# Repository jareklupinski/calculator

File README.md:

# calculator
An open TI-84-inspired mathematical device

This design will be fun to play with for a while.

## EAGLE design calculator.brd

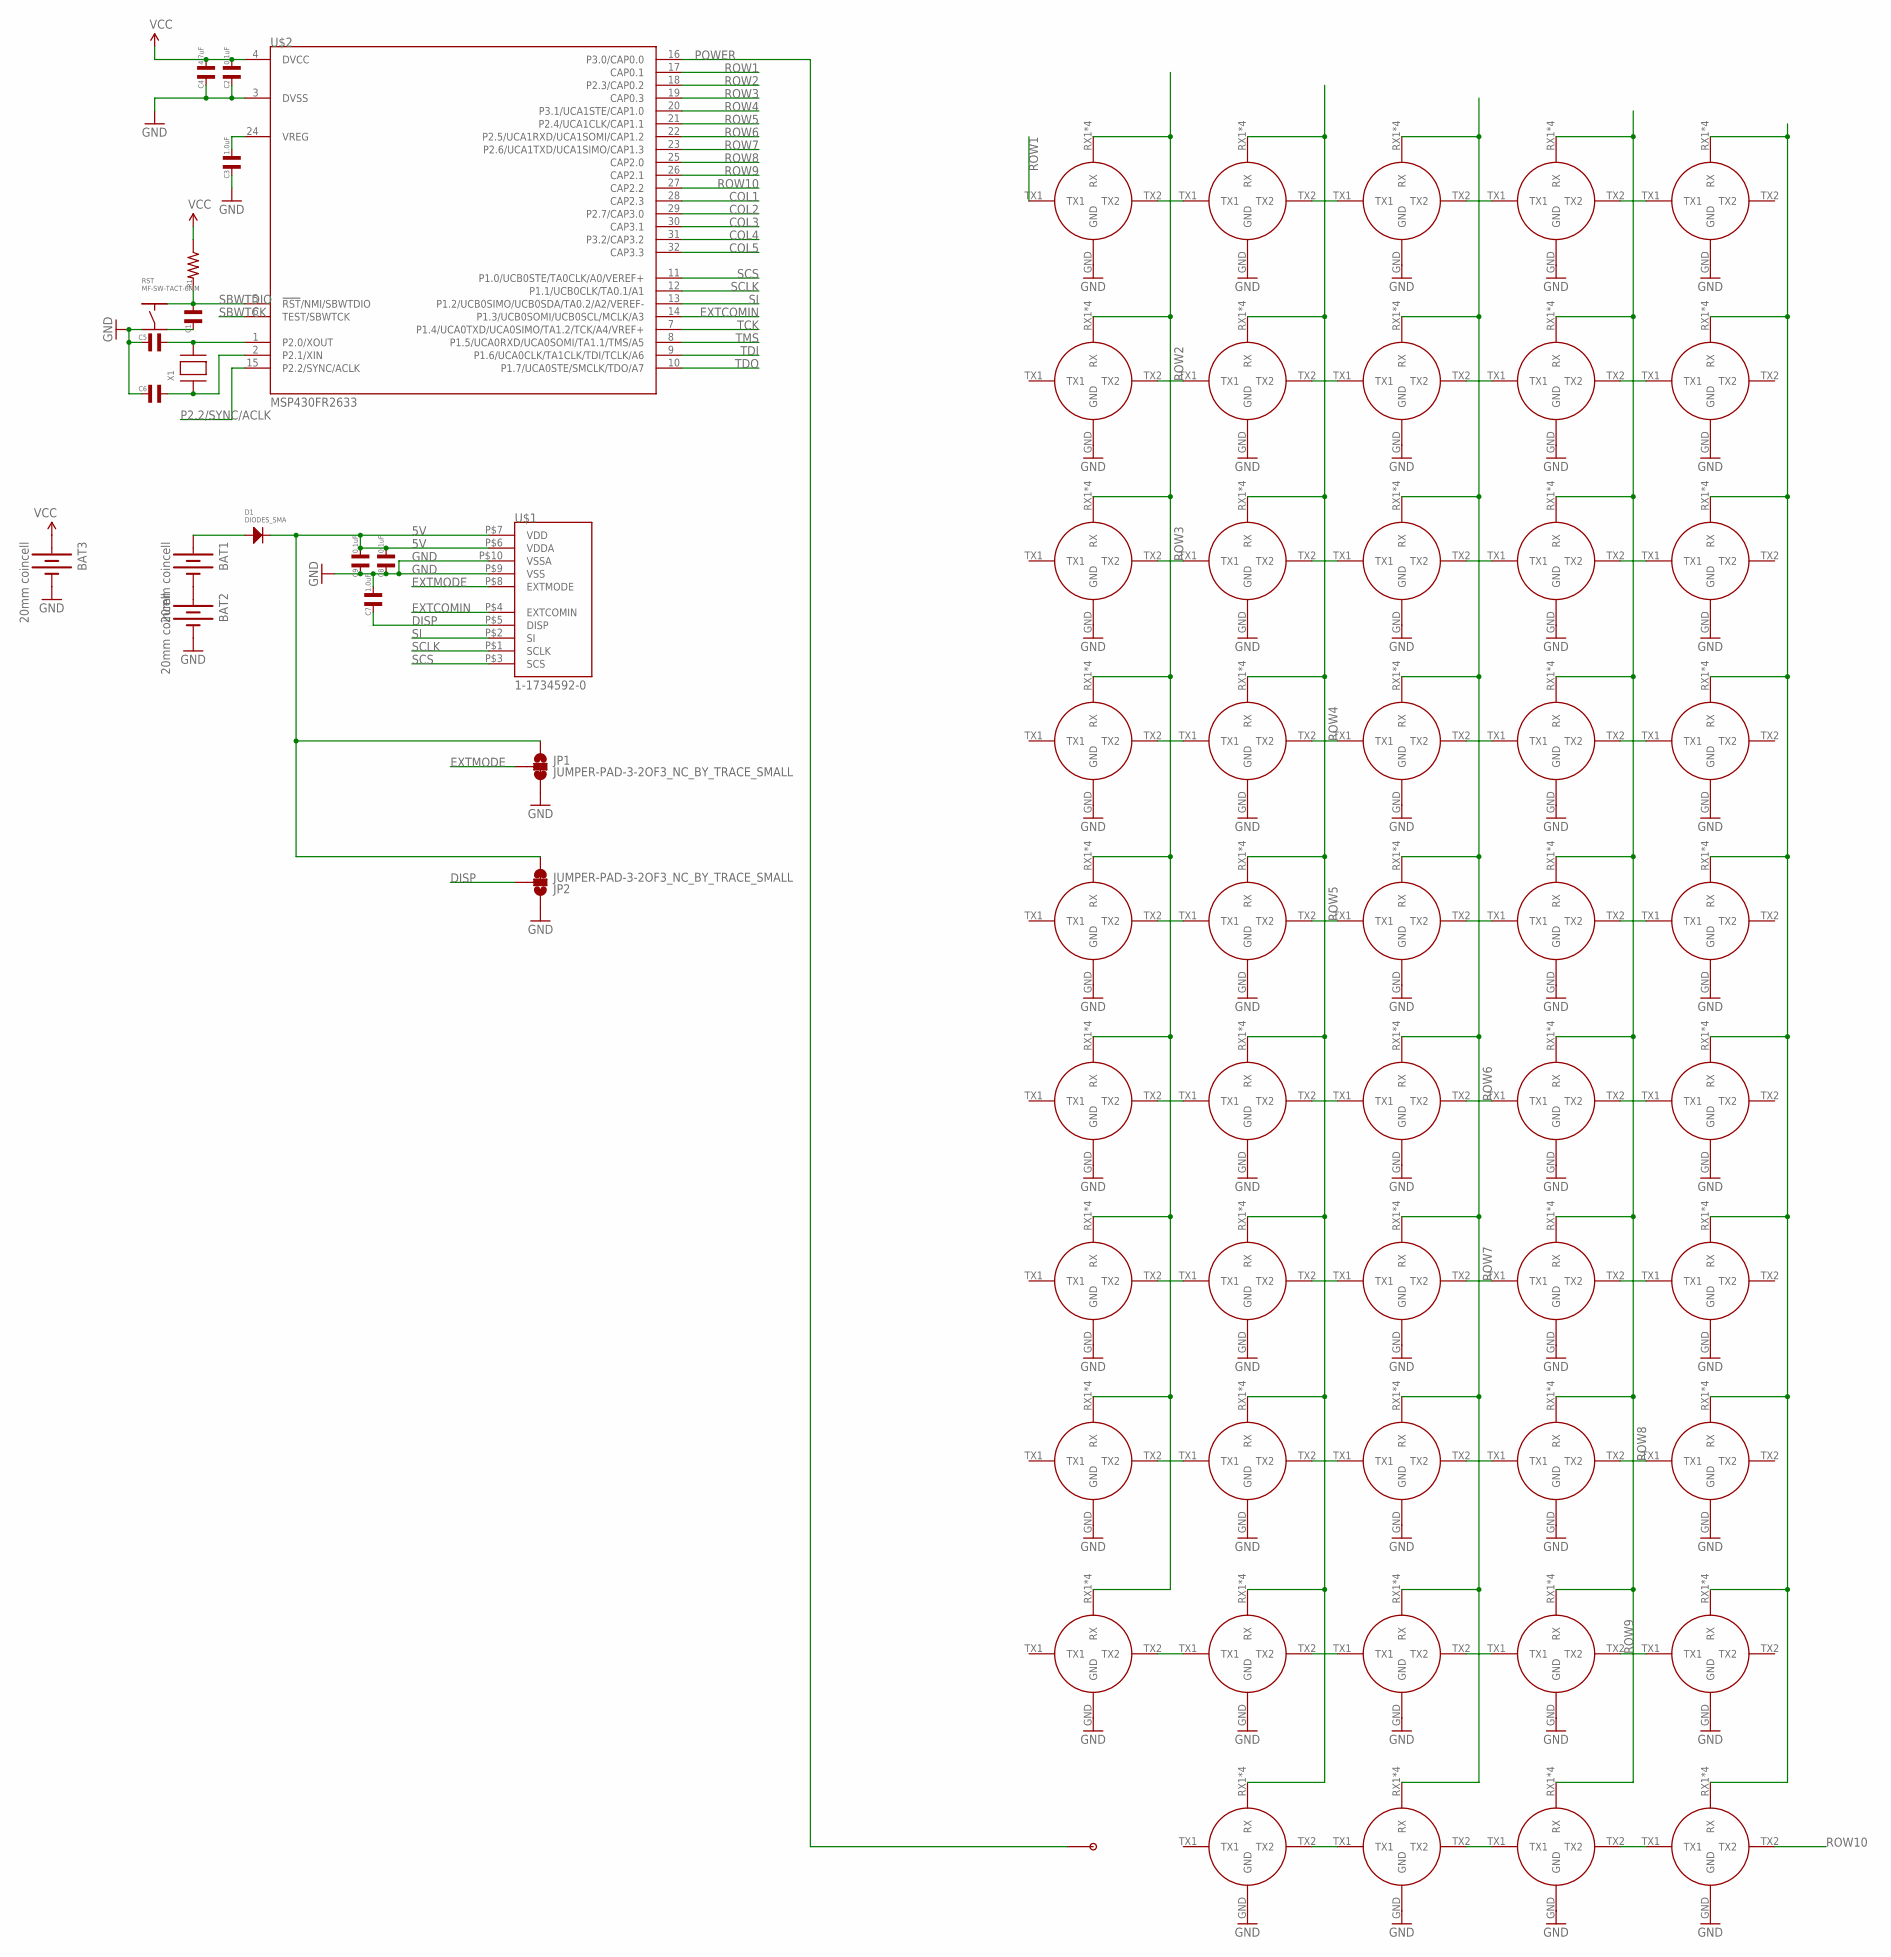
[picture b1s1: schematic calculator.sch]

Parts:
BAT1, BAT2, BAT3: 20mm coincell; BATTCON_20MM_4LEGS
C1: CAPACITOR_NP_0603; C0603
C2, C8, C9: 0.1uF; C0603
C3, C7: 1.0uF; C0603
C4: 4.7uF; C0603
C5, C6: CAPACITOR_NP_0402; C0402
D1: DIODES_SMA; SMA
JP1, JP2: JUMPER-PAD-3-2OF3_NC_BY_TRACE_SMALL; PAD-JUMPER-3-2OF3_NC_BY_TRACE_YES_SILK_FULL_BOX
P1: CAPPADPAD; CAPTOUCHBTN2
R1: RESISTOR_0603; R0603
RST: MF-SW-TACT-6MM; TACT6MM
U$1: 1-1734592-0
U$2: MSP430FR2633; TSSOP32
U$3, U$4, U$5, U$6, U$7, U$8, U$9, U$10, U$11, U$12, U$13, U$14, U$15, U$16, U$17, U$18, U$19, U$20, U$21, U$22, U$23, U$24, U$25, U$26, U$27, U$28, U$29, U$30, U$31, U$32, U$33, U$34, U$35, U$36, U$37, U$38, U$39, U$40, U$41, U$42, U$43, U$44, U$45, U$46, U$47, U$48, U$49, U$50, U$51: CAPTOUCH; CAPTOUCHBTN
X1: XTAL-3.2X1.5; XTAL3215

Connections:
5V: C8.P$1, C9.P$1, D1.CATHODE, JP1.1, JP2.3, U$1.P$6 (VDDA), U$1.P$7 (VDD)
COL1: U$2.28 (CAP2.3), U$3.RX1 (RX), U$3.RX2 (RX), U$3.RX3 (RX), U$3.RX4 (RX), U$8.RX1 (RX), U$8.RX2 (RX), U$8.RX3 (RX), U$8.RX4 (RX), U$13.RX1 (RX), U$13.RX2 (RX), U$13.RX3 (RX), U$13.RX4 (RX), U$18.RX1 (RX), U$18.RX2 (RX), U$18.RX3 (RX), U$18.RX4 (RX), U$23.RX1 (RX), U$23.RX2 (RX), U$23.RX3 (RX), U$23.RX4 (RX), U$28.RX1 (RX), U$28.RX2 (RX), U$28.RX3 (RX), U$28.RX4 (RX), U$33.RX1 (RX), U$33.RX2 (RX), U$33.RX3 (RX), U$33.RX4 (RX), U$38.RX1 (RX), U$38.RX2 (RX), U$38.RX3 (RX), U$38.RX4 (RX), U$43.RX1 (RX), U$43.RX2 (RX), U$43.RX3 (RX), U$43.RX4 (RX)
COL2: U$2.29 (P2.7/CAP3.0), U$4.RX1 (RX), U$4.RX2 (RX), U$4.RX3 (RX), U$4.RX4 (RX), U$9.RX1 (RX), U$9.RX2 (RX), U$9.RX3 (RX), U$9.RX4 (RX), U$14.RX1 (RX), U$14.RX2 (RX), U$14.RX3 (RX), U$14.RX4 (RX), U$19.RX1 (RX), U$19.RX2 (RX), U$19.RX3 (RX), U$19.RX4 (RX), U$24.RX1 (RX), U$24.RX2 (RX), U$24.RX3 (RX), U$24.RX4 (RX), U$29.RX1 (RX), U$29.RX2 (RX), U$29.RX3 (RX), U$29.RX4 (RX), U$34.RX1 (RX), U$34.RX2 (RX), U$34.RX3 (RX), U$34.RX4 (RX), U$39.RX1 (RX), U$39.RX2 (RX), U$39.RX3 (RX), U$39.RX4 (RX), U$44.RX1 (RX), U$44.RX2 (RX), U$44.RX3 (RX), U$44.RX4 (RX), U$48.RX1 (RX), U$48.RX2 (RX), U$48.RX3 (RX), U$48.RX4 (RX)
COL3: U$2.30 (CAP3.1), U$5.RX1 (RX), U$5.RX2 (RX), U$5.RX3 (RX), U$5.RX4 (RX), U$10.RX1 (RX), U$10.RX2 (RX), U$10.RX3 (RX), U$10.RX4 (RX), U$15.RX1 (RX), U$15.RX2 (RX), U$15.RX3 (RX), U$15.RX4 (RX), U$20.RX1 (RX), U$20.RX2 (RX), U$20.RX3 (RX), U$20.RX4 (RX), U$25.RX1 (RX), U$25.RX2 (RX), U$25.RX3 (RX), U$25.RX4 (RX), U$30.RX1 (RX), U$30.RX2 (RX), U$30.RX3 (RX), U$30.RX4 (RX), U$35.RX1 (RX), U$35.RX2 (RX), U$35.RX3 (RX), U$35.RX4 (RX), U$40.RX1 (RX), U$40.RX2 (RX), U$40.RX3 (RX), U$40.RX4 (RX), U$45.RX1 (RX), U$45.RX2 (RX), U$45.RX3 (RX), U$45.RX4 (RX), U$49.RX1 (RX), U$49.RX2 (RX), U$49.RX3 (RX), U$49.RX4 (RX)
COL4: U$2.31 (P3.2/CAP3.2), U$6.RX1 (RX), U$6.RX2 (RX), U$6.RX3 (RX), U$6.RX4 (RX), U$11.RX1 (RX), U$11.RX2 (RX), U$11.RX3 (RX), U$11.RX4 (RX), U$16.RX1 (RX), U$16.RX2 (RX), U$16.RX3 (RX), U$16.RX4 (RX), U$21.RX1 (RX), U$21.RX2 (RX), U$21.RX3 (RX), U$21.RX4 (RX), U$26.RX1 (RX), U$26.RX2 (RX), U$26.RX3 (RX), U$26.RX4 (RX), U$31.RX1 (RX), U$31.RX2 (RX), U$31.RX3 (RX), U$31.RX4 (RX), U$36.RX1 (RX), U$36.RX2 (RX), U$36.RX3 (RX), U$36.RX4 (RX), U$41.RX1 (RX), U$41.RX2 (RX), U$41.RX3 (RX), U$41.RX4 (RX), U$46.RX1 (RX), U$46.RX2 (RX), U$46.RX3 (RX), U$46.RX4 (RX), U$50.RX1 (RX), U$50.RX2 (RX), U$50.RX3 (RX), U$50.RX4 (RX)
COL5: U$2.32 (CAP3.3), U$7.RX1 (RX), U$7.RX2 (RX), U$7.RX3 (RX), U$7.RX4 (RX), U$12.RX1 (RX), U$12.RX2 (RX), U$12.RX3 (RX), U$12.RX4 (RX), U$17.RX1 (RX), U$17.RX2 (RX), U$17.RX3 (RX), U$17.RX4 (RX), U$22.RX1 (RX), U$22.RX2 (RX), U$22.RX3 (RX), U$22.RX4 (RX), U$27.RX1 (RX), U$27.RX2 (RX), U$27.RX3 (RX), U$27.RX4 (RX), U$32.RX1 (RX), U$32.RX2 (RX), U$32.RX3 (RX), U$32.RX4 (RX), U$37.RX1 (RX), U$37.RX2 (RX), U$37.RX3 (RX), U$37.RX4 (RX), U$42.RX1 (RX), U$42.RX2 (RX), U$42.RX3 (RX), U$42.RX4 (RX), U$47.RX1 (RX), U$47.RX2 (RX), U$47.RX3 (RX), U$47.RX4 (RX), U$51.RX1 (RX), U$51.RX2 (RX), U$51.RX3 (RX), U$51.RX4 (RX)
DISP: C7.P$2, JP2.2, U$1.P$5 (DISP)
EXTCOMIN: U$1.P$4 (EXTCOMIN), U$2.14 (P1.3/UCB0SOMI/UCB0SCL/MCLK/A3)
EXTMODE: JP1.2, U$1.P$8 (EXTMODE)
GND: BAT2.NEGATIVE (-), BAT3.NEGATIVE (-), C2.P$2, C3.P$2, C4.P$2, C5.P$2, C6.P$2, C7.P$1, C8.P$2, C9.P$2, JP1.3, JP2.1, RST.P$3, U$1.P$9 (VSS), U$1.P$10 (VSSA), U$2.3 (DVSS), U$3.GND, U$4.GND, U$5.GND, U$6.GND, U$7.GND, U$8.GND, U$9.GND, U$10.GND, U$11.GND, U$12.GND, U$13.GND, U$14.GND, U$15.GND, U$16.GND, U$17.GND, U$18.GND, U$19.GND, U$20.GND, U$21.GND, U$22.GND, U$23.GND, U$24.GND, U$25.GND, U$26.GND, U$27.GND, U$28.GND, U$29.GND, U$30.GND, U$31.GND, U$32.GND, U$33.GND, U$34.GND, U$35.GND, U$36.GND, U$37.GND, U$38.GND, U$39.GND, U$40.GND, U$41.GND, U$42.GND, U$43.GND, U$44.GND, U$45.GND, U$46.GND, U$47.GND, U$48.GND, U$49.GND, U$50.GND, U$51.GND
unnamed: BAT1.NEGATIVE (-), BAT2.POSITIVE@1 (+), BAT2.POSITIVE@2 (+), BAT2.POSITIVE@3 (+), BAT2.POSITIVE@4 (+)
unnamed: C3.P$1, U$2.24 (VREG)
unnamed: C1.P$2, RST.P$4
unnamed: BAT1.POSITIVE@1 (+), BAT1.POSITIVE@2 (+), BAT1.POSITIVE@3 (+), BAT1.POSITIVE@4 (+), D1.ANODE
unnamed: C5.P$1, U$2.1 (P2.0/XOUT), X1.P$2
unnamed: C6.P$1, U$2.2 (P2.1/XIN), X1.P$1
unnamed: U$3.TX2, U$4.TX1
unnamed: U$4.TX2, U$5.TX1
unnamed: U$5.TX2, U$6.TX1
unnamed: U$6.TX2, U$7.TX1
unnamed: U$18.TX2, U$19.TX1
unnamed: U$9.TX2, U$10.TX1
unnamed: U$10.TX2, U$11.TX1
unnamed: U$11.TX2, U$12.TX1
unnamed: U$14.TX2, U$15.TX1
unnamed: U$15.TX2, U$16.TX1
unnamed: U$16.TX2, U$17.TX1
unnamed: U$20.TX2, U$21.TX1
unnamed: U$21.TX2, U$22.TX1
unnamed: U$23.TX2, U$24.TX1
unnamed: U$25.TX2, U$26.TX1
unnamed: U$26.TX2, U$27.TX1
unnamed: U$28.TX2, U$29.TX1
unnamed: U$29.TX2, U$30.TX1
unnamed: U$31.TX2, U$32.TX1
unnamed: U$33.TX2, U$34.TX1
unnamed: U$34.TX2, U$35.TX1
unnamed: U$36.TX2, U$37.TX1
unnamed: U$38.TX2, U$39.TX1
unnamed: U$39.TX2, U$40.TX1
unnamed: U$40.TX2, U$41.TX1
unnamed: U$43.TX2, U$44.TX1
unnamed: U$44.TX2, U$45.TX1
unnamed: U$45.TX2, U$46.TX1
unnamed: U$48.TX2, U$49.TX1
unnamed: U$49.TX2, U$50.TX1
unnamed: U$50.TX2, U$51.TX1
P2.2/SYNC/ACLK: U$2.15 (P2.2/SYNC/ACLK)
POWER: P1.RX, U$2.16 (P3.0/CAP0.0)
ROW1: U$2.17 (CAP0.1), U$3.TX1
ROW2: U$2.18 (P2.3/CAP0.2), U$8.TX2, U$9.TX1
ROW3: U$2.19 (CAP0.3), U$13.TX2, U$14.TX1
ROW4: U$2.20 (P3.1/UCA1STE/CAP1.0), U$19.TX2, U$20.TX1
ROW5: U$2.21 (P2.4/UCA1CLK/CAP1.1), U$24.TX2, U$25.TX1
ROW6: U$2.22 (P2.5/UCA1RXD/UCA1SOMI/CAP1.2), U$30.TX2, U$31.TX1
ROW7: U$2.23 (P2.6/UCA1TXD/UCA1SIMO/CAP1.3), U$35.TX2, U$36.TX1
ROW8: U$2.25 (CAP2.0), U$41.TX2, U$42.TX1
ROW9: U$2.26 (CAP2.1), U$46.TX2, U$47.TX1
ROW10: U$2.27 (CAP2.2), U$51.TX2
SBWTCK: U$2.6 (TEST/SBWTCK)
SBWTDIO: C1.P$1, R1.P$2, RST.P$2, U$2.5 (!RST!/NMI/SBWTDIO)
SCLK: U$1.P$1 (SCLK), U$2.12 (P1.1/UCB0CLK/TA0.1/A1)
SCS: U$1.P$3 (SCS), U$2.11 (P1.0/UCB0STE/TA0CLK/A0/VEREF+)
SI: U$1.P$2 (SI), U$2.13 (P1.2/UCB0SIMO/UCB0SDA/TA0.2/A2/VEREF-)
TCK: U$2.7 (P1.4/UCA0TXD/UCA0SIMO/TA1.2/TCK/A4/VREF+)
TDI: U$2.9 (P1.6/UCA0CLK/TA1CLK/TDI/TCLK/A6)
TDO: U$2.10 (P1.7/UCA0STE/SMCLK/TDO/A7)
TMS: U$2.8 (P1.5/UCA0RXD/UCA0SOMI/TA1.1/TMS/A5)
VCC: BAT3.POSITIVE@1 (+), BAT3.POSITIVE@2 (+), BAT3.POSITIVE@3 (+), BAT3.POSITIVE@4 (+), C2.P$1, C4.P$1, R1.P$1, U$2.4 (DVCC)

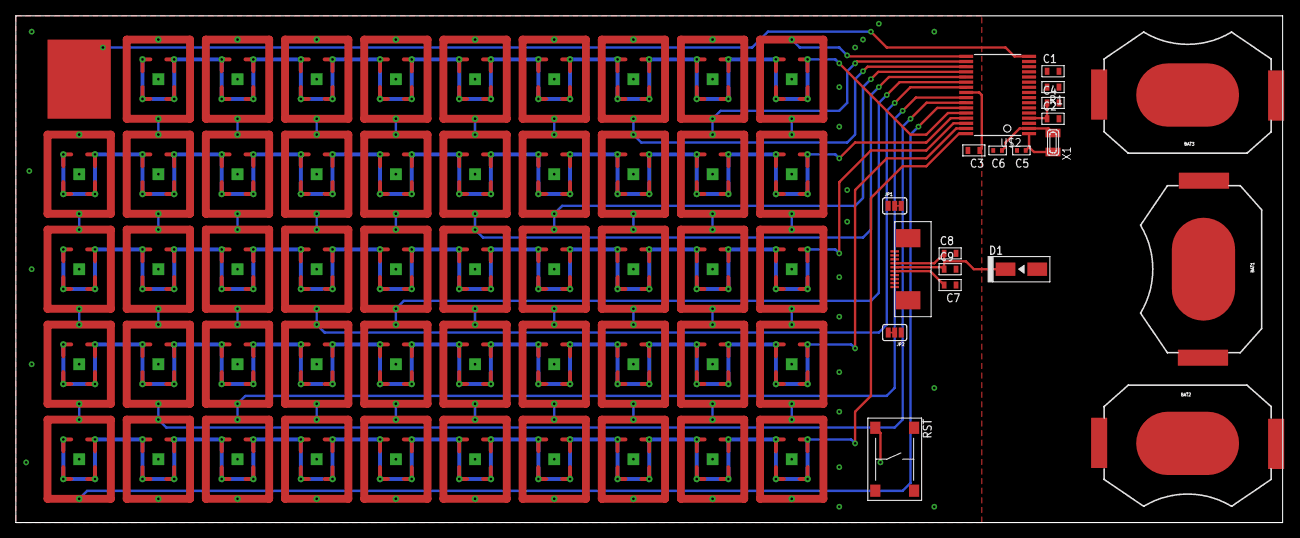
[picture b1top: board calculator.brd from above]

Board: 2 copper layers, 160.0 x 64.0 mm, 70 parts (0 on the bottom side), 63 nets.

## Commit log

2018-07-04 design started

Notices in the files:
parts and their libraries:
SparkFun-Passives: Licensing: Creative Commons ShareAlike 4.0 International - https://creativecommons.org/licenses/by-sa/4.0
